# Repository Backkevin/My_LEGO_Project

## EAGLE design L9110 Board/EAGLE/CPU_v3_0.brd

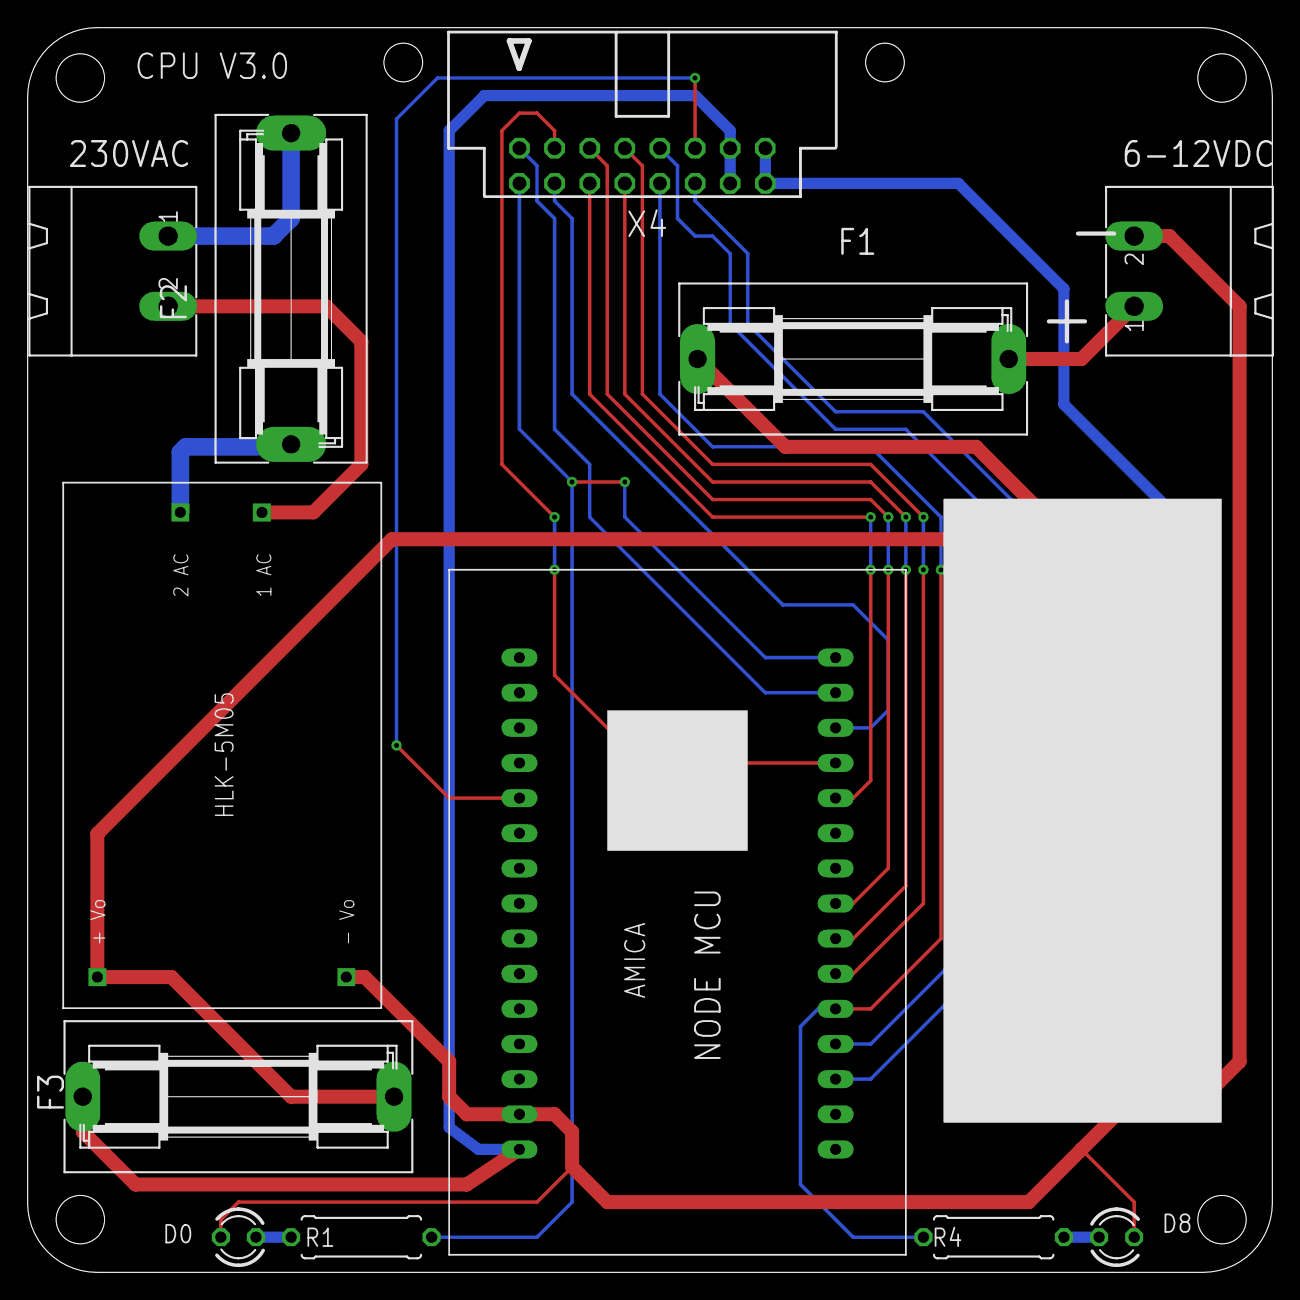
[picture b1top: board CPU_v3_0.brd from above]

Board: 2 copper layers, 90.0 x 90.0 mm, 13 parts (0 on the bottom side), 23 nets.

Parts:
6-12VDC, 230VAC: MSTBA2
D0, D8: LED3MM
F1, F2, F3: SH22,5A
R1, R4: 470R; 0309/10
U$1: NODEMCUESP8266
U$2: CP8-ADJ
U$3: 5VDC/5W; HLK-5M05
X4: 057-016-0

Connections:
+5VDC: F3.1, U$1.1, X4.13, X4.14
D0: R1.2, U$1.16, X4.1
D8: R4.2, U$1.26, X4.9
D9: U$1.11, X4.12
GND: D0.K, D8.K, U$1.2, U$2.OUT-, U$3.3, X4.15, X4.16
unnamed: D8.A, R4.1
unnamed: F3.2, U$2.OUT+, U$3.4
unnamed: U$1.19, X4.4
unnamed: D0.A, R1.1
unnamed: 230VAC.1, F2.2
unnamed: F2.1, U$3.1
unnamed: 230VAC.2, U$3.2
unnamed: 6-12VDC.1, F1.2
unnamed: F1.1, U$2.IN+
unnamed: 6-12VDC.2, U$2.IN-
unnamed: U$1.20, X4.5
unnamed: U$1.23, X4.6
unnamed: U$1.24, X4.7
unnamed: U$1.25, X4.8
RX: U$1.27, X4.10
SCL: U$1.17, X4.2
SDA: U$1.18, X4.3
TX: U$1.28, X4.11

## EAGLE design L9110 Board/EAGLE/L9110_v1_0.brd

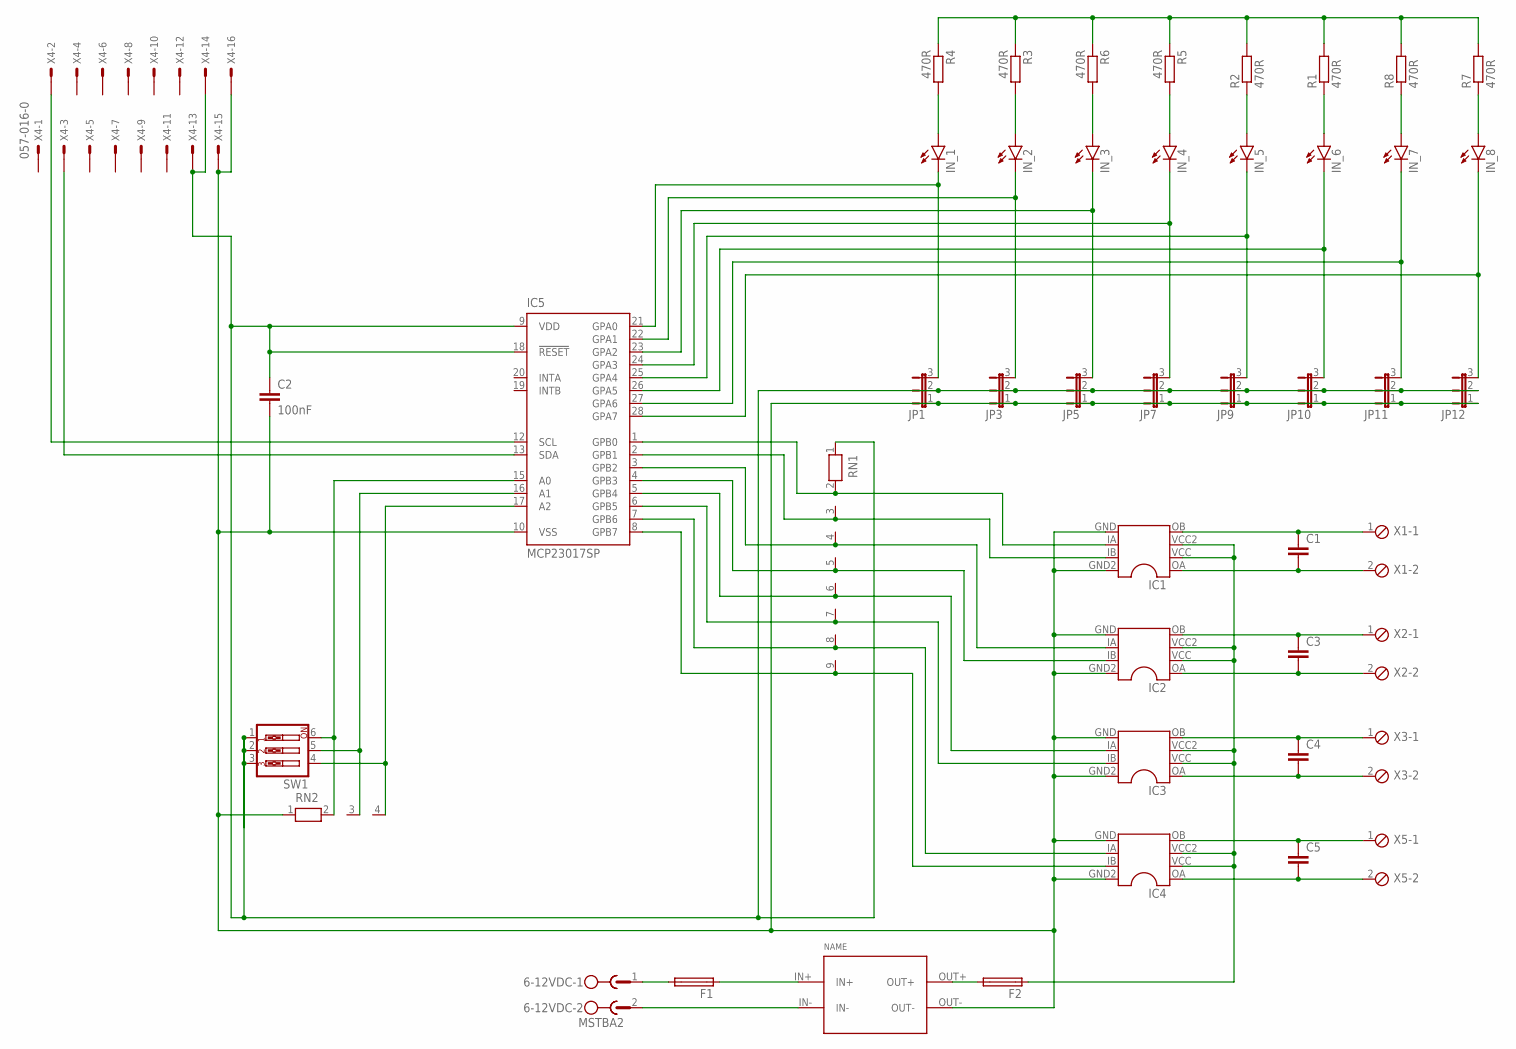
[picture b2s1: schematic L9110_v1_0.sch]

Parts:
6-12VDC: MSTBA2
C1, C3, C4, C5: C-EU025-024X044; C025-024X044
C2: 100nF; C025-024X044
F1, F2: SH22,5A
IC1, IC2, IC3, IC4: L9110
IC5: MCP23017SP; DIL28-3
IN_1, IN_2, IN_3, IN_4, IN_5, IN_6, IN_7, IN_8: LED3MM
JP1, JP3, JP5, JP7, JP9, JP10, JP11, JP12: JP2E; JP2
R1, R2, R3, R4, R5, R6, R7, R8: 470R; 0309/10
RN1: RN08; RN-9
RN2: RN03; RN-3
SW1: SW_DIP-3; EDG-03
U$2: CP8-ADJ
X1, X2, X3, X5: MPT2; 2POL254
X4: 057-016-0

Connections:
GND2: C2.2, IC1.GND (5), IC1.GND2 (8), IC2.GND (5), IC2.GND2 (8), IC3.GND (5), IC3.GND2 (8), IC4.GND (5), IC4.GND2 (8), IC5.10 (VSS), JP1.1, JP3.1, JP5.1, JP7.1, JP9.1, JP10.1, JP11.1, JP12.1, RN2.1, U$2.OUT-, X4.15, X4.16
unnamed: IC1.IA (6), IC5.1 (GPB0), RN1.2
unnamed: IC5.22 (GPA1), IN_2.K (C), JP3.3
unnamed: IC1.IB (7), IC5.2 (GPB1), RN1.3
unnamed: IC5.24 (GPA3), IN_4.K (C), JP7.3
unnamed: IC2.IA (6), IC5.3 (GPB2), RN1.4
unnamed: IC5.17 (A2), RN2.4, SW1.4
unnamed: IC5.26 (GPA5), IN_6.K (C), JP10.3
unnamed: IC2.IB (7), IC5.4 (GPB3), RN1.5
unnamed: IC5.28 (GPA7), IN_8.K (C), JP12.3
unnamed: IN_8.A, R7.1
unnamed: IN_7.A, R8.1
unnamed: IC3.IA (6), IC5.5 (GPB4), RN1.6
unnamed: IN_6.A, R1.1
unnamed: IC3.IB (7), IC5.6 (GPB5), RN1.7
unnamed: IC4.IA (6), IC5.7 (GPB6), RN1.8
unnamed: IC4.IB (7), IC5.8 (GPB7), RN1.9
unnamed: C1.1, IC1.OB (4), X1.1
unnamed: F2.1, IC1.VCC (2), IC1.VCC2 (3), IC2.VCC (2), IC2.VCC2 (3), IC3.VCC (2), IC3.VCC2 (3), IC4.VCC (2), IC4.VCC2 (3)
unnamed: C1.2, IC1.OA (1), X1.2
unnamed: C3.1, IC2.OB (4), X2.1
unnamed: IC5.21 (GPA0), IN_1.K (C), JP1.3
unnamed: C3.2, IC2.OA (1), X2.2
unnamed: IC5.23 (GPA2), IN_3.K (C), JP5.3
unnamed: C4.1, IC3.OB (4), X3.1
unnamed: IC5.25 (GPA4), IN_5.K (C), JP9.3
unnamed: C4.2, IC3.OA (1), X3.2
unnamed: IC5.27 (GPA6), IN_7.K (C), JP11.3
unnamed: C5.1, IC4.OB (4), X5.1
unnamed: IN_5.A, R2.1
unnamed: IN_4.A, R5.2
unnamed: IN_3.A, R6.2
unnamed: IN_2.A, R3.2
unnamed: IN_1.A, R4.2
unnamed: C5.2, IC4.OA (1), X5.2
unnamed: IC5.16 (A1), RN2.3, SW1.5
unnamed: 6-12VDC.1, F1.2
unnamed: F1.1, U$2.IN+
unnamed: 6-12VDC.2, U$2.IN-
unnamed: F2.2, U$2.OUT+
unnamed: IC5.12 (SCL), X4.2
unnamed: IC5.13 (SDA), X4.3
unnamed: IC5.15 (A0), RN2.2, SW1.6
VCC5.1: C2.1, IC5.9 (VDD), IC5.18 (!RESET), JP1.2, JP3.2, JP5.2, JP7.2, JP9.2, JP10.2, JP11.2, JP12.2, RN1.1, SW1.1, SW1.2, SW1.3, X4.13, X4.14
VCC5.2: R1.2, R2.2, R3.1, R4.1, R5.1, R6.1, R7.2, R8.2

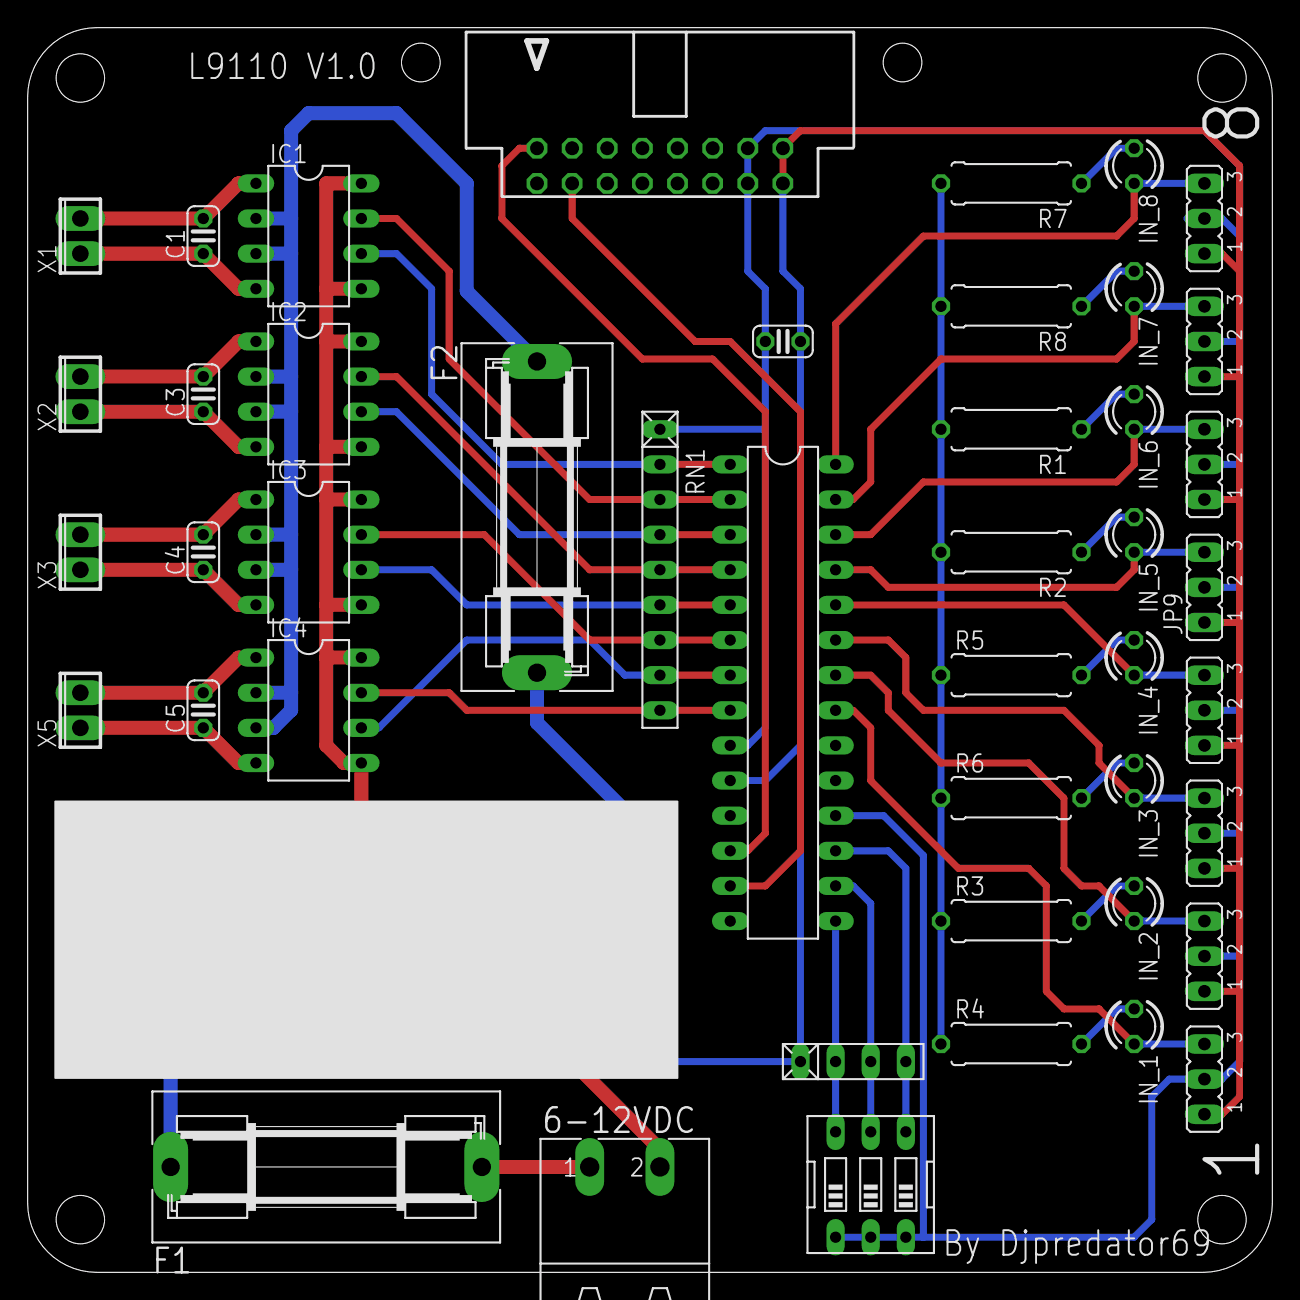
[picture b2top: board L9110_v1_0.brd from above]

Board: 2 copper layers, 90.0 x 90.0 mm, 46 parts (0 on the bottom side), 45 nets.

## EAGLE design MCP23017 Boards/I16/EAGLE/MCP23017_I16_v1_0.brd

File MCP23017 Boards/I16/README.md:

# MCP23017 Boards
+ I16
	+ V1.0
		* Work 50%
		* Partlist not OK
		* [GERBER FILES](https://github.com/Backkevin/My_LEGO_Project/tree/master/MCP23017%20Boards/I16/GERBER%20FILES)
		* [EAGLE FILES](https://github.com/Backkevin/My_LEGO_Project/tree/master/MCP23017%20Boards/I16/EAGLE)
		* [PDF FILES](https://github.com/Backkevin/My_LEGO_Project/tree/master/MCP23017%20Boards/I16/PDF)
	+ Work in progress !

### Partslist INPUT
                    
  Part Name   |      PIC      |   Part Info            | Part Quantity |   Part Link 
------------- | ------------- | ---------------------- | ------------- | -------------

### Partslist CPU
                    
  Part Name   |      PIC      |   Part Info            | Part Quantity |   Part Link 
------------- | ------------- | ---------------------- | ------------- | -------------

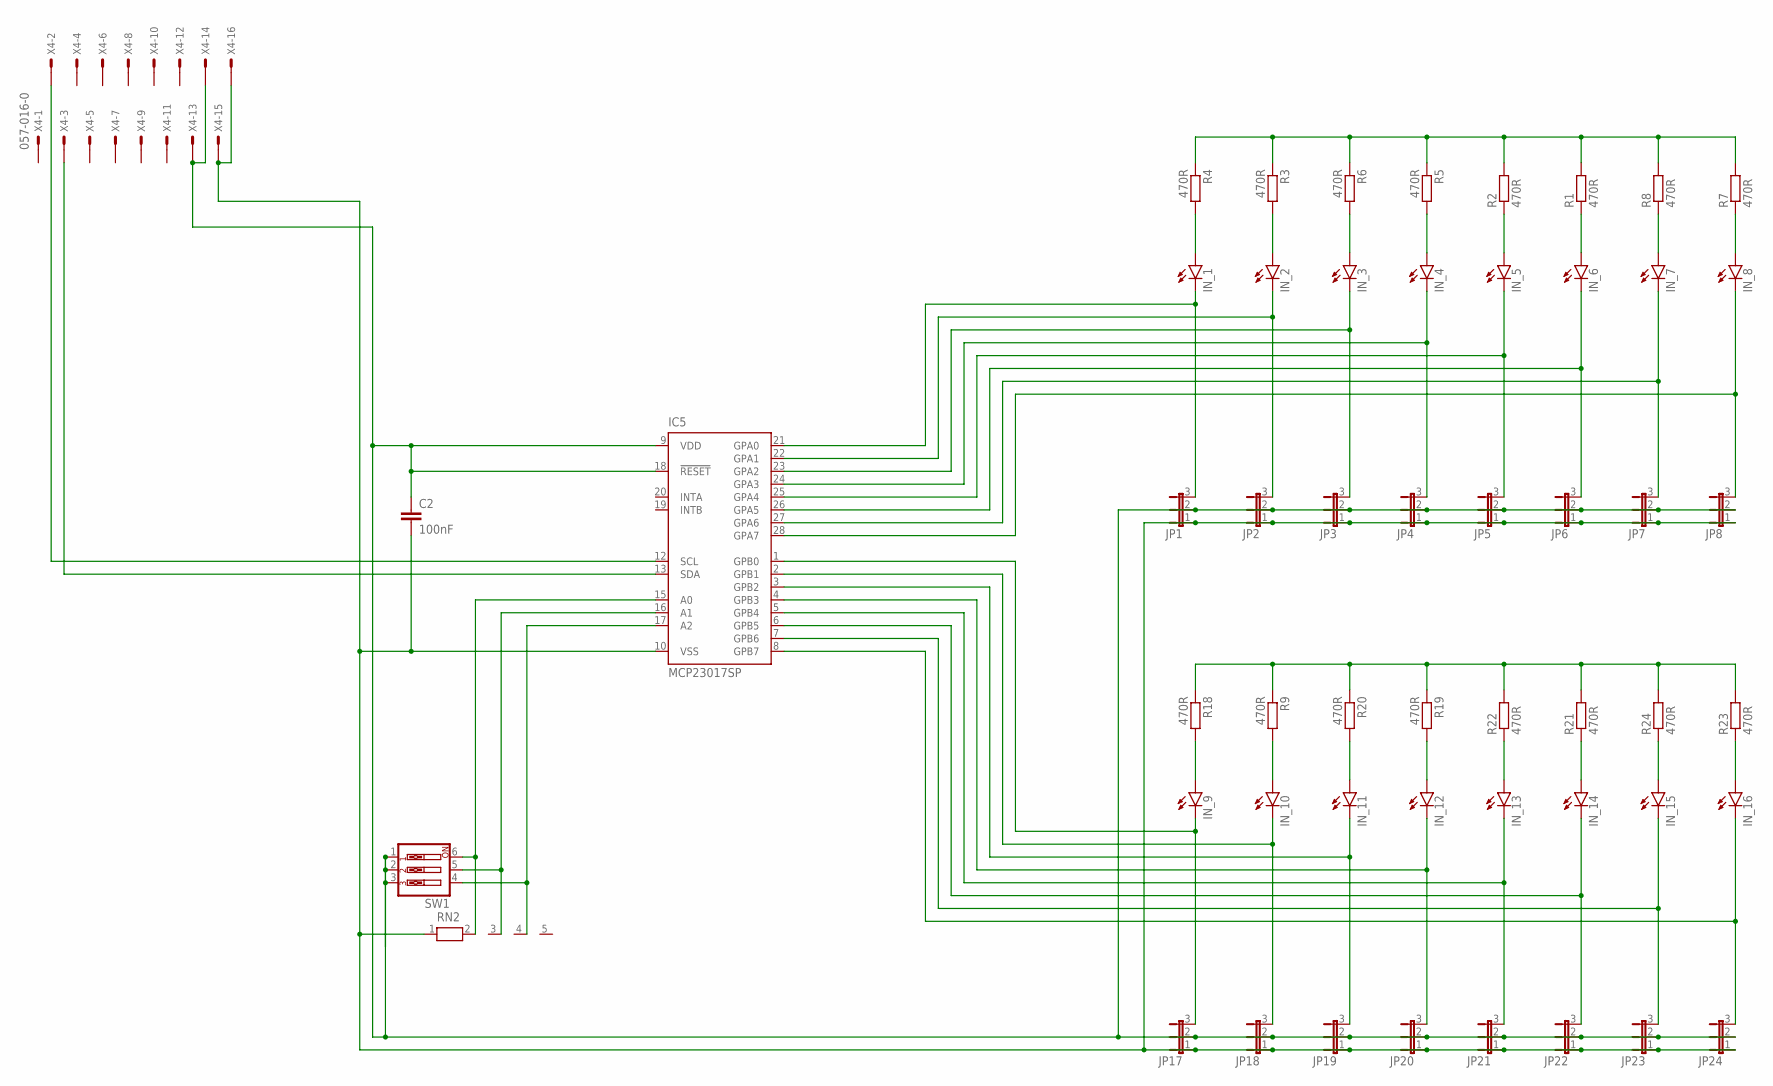
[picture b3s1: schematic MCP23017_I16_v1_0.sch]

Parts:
C2: 100nF; C025-024X044
IC5: MCP23017SP; DIL28-3
IN_1, IN_2, IN_3, IN_4, IN_5, IN_6, IN_7, IN_8, IN_9, IN_10, IN_11, IN_12, IN_13, IN_14, IN_15, IN_16: LED3MM
JP1, JP2, JP3, JP4, JP5, JP6, JP7, JP8, JP17, JP18, JP19, JP20, JP21, JP22, JP23, JP24: JP2E; JP2
R1, R2, R3, R4, R5, R6, R7, R8, R9, R18, R19, R20, R21, R22, R23, R24: 470R; 0309/10
RN2: RN04; RN-5
SW1: SW_DIP-3; EDG-03
X4: 057-016-0

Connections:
GND1: C2.2, IC5.10 (VSS), JP1.1, JP2.1, JP3.1, JP4.1, JP5.1, JP6.1, JP7.1, JP8.1, JP17.1, JP18.1, JP19.1, JP20.1, JP21.1, JP22.1, JP23.1, JP24.1, RN2.1, X4.15, X4.16
unnamed: IC5.21 (GPA0), IN_1.K (C), JP1.3
unnamed: IC5.15 (A0), RN2.2, SW1.6
unnamed: IC5.23 (GPA2), IN_3.K (C), JP3.3
unnamed: IC5.25 (GPA4), IN_5.K (C), JP5.3
unnamed: IC5.17 (A2), RN2.4, SW1.4
unnamed: IC5.27 (GPA6), IN_7.K (C), JP7.3
unnamed: IN_8.A, R7.1
unnamed: IN_7.A, R8.1
unnamed: IN_6.A, R1.1
unnamed: IC5.22 (GPA1), IN_2.K (C), JP2.3
unnamed: IC5.24 (GPA3), IN_4.K (C), JP4.3
unnamed: IC5.26 (GPA5), IN_6.K (C), JP6.3
unnamed: IC5.28 (GPA7), IN_8.K (C), JP8.3
unnamed: IN_5.A, R2.1
unnamed: IN_4.A, R5.2
unnamed: IN_3.A, R6.2
unnamed: IN_2.A, R3.2
unnamed: IN_1.A, R4.2
unnamed: IC5.16 (A1), RN2.3, SW1.5
unnamed: IC5.1 (GPB0), IN_9.K (C), JP17.3
unnamed: IC5.3 (GPB2), IN_11.K (C), JP19.3
unnamed: IC5.5 (GPB4), IN_13.K (C), JP21.3
unnamed: IC5.2 (GPB1), IN_10.K (C), JP18.3
unnamed: IC5.4 (GPB3), IN_12.K (C), JP20.3
unnamed: IC5.7 (GPB6), IN_15.K (C), JP23.3
unnamed: IC5.6 (GPB5), IN_14.K (C), JP22.3
unnamed: IC5.8 (GPB7), IN_16.K (C), JP24.3
unnamed: IN_16.A, R23.1
unnamed: IN_15.A, R24.1
unnamed: IN_14.A, R21.1
unnamed: IN_13.A, R22.1
unnamed: IN_12.A, R19.2
unnamed: IN_11.A, R20.2
unnamed: IN_10.A, R9.2
unnamed: IN_9.A, R18.2
unnamed: IC5.12 (SCL), X4.2
unnamed: IC5.13 (SDA), X4.3
VCC5.2: C2.1, IC5.9 (VDD), IC5.18 (!RESET), JP1.2, JP2.2, JP3.2, JP4.2, JP5.2, JP6.2, JP7.2, JP8.2, JP17.2, JP18.2, JP19.2, JP20.2, JP21.2, JP22.2, JP23.2, JP24.2, R1.2, R2.2, R3.1, R4.1, R5.1, R6.1, R7.2, R8.2, R9.1, R18.1, R19.1, R20.1, R21.2, R22.2, R23.2, R24.2, SW1.1, SW1.2, SW1.3, X4.13, X4.14

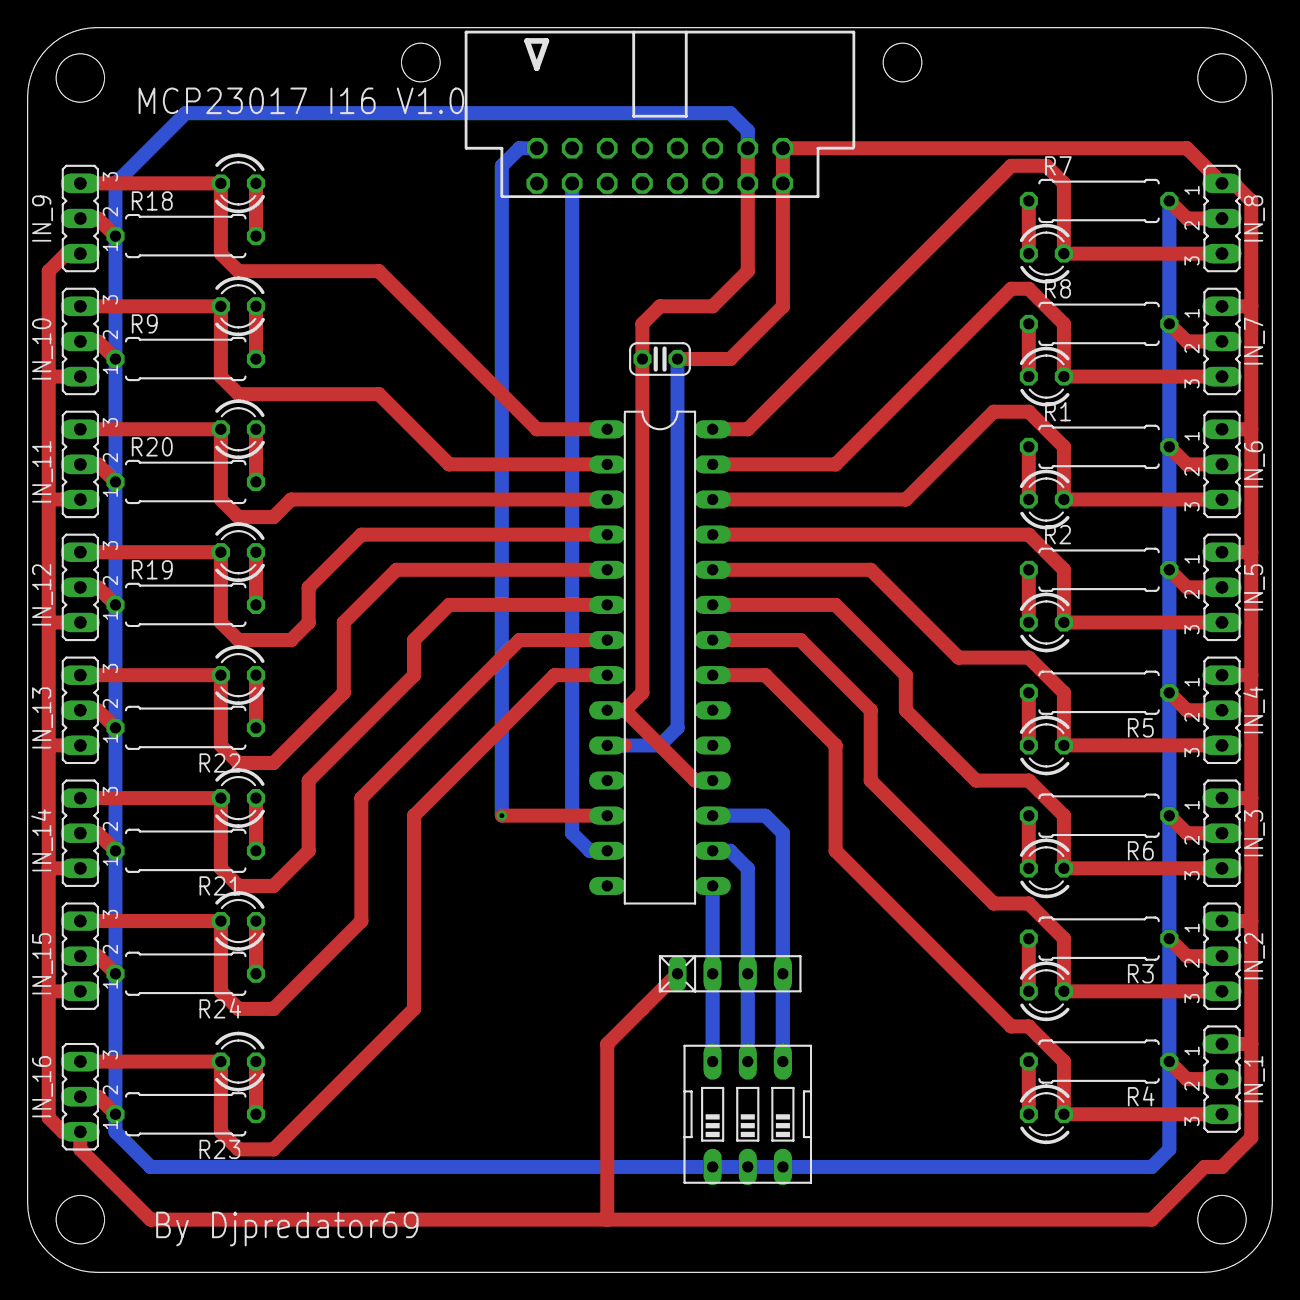
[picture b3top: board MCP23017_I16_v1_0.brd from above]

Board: 2 copper layers, 90.0 x 90.0 mm, 53 parts (0 on the bottom side), 39 nets.

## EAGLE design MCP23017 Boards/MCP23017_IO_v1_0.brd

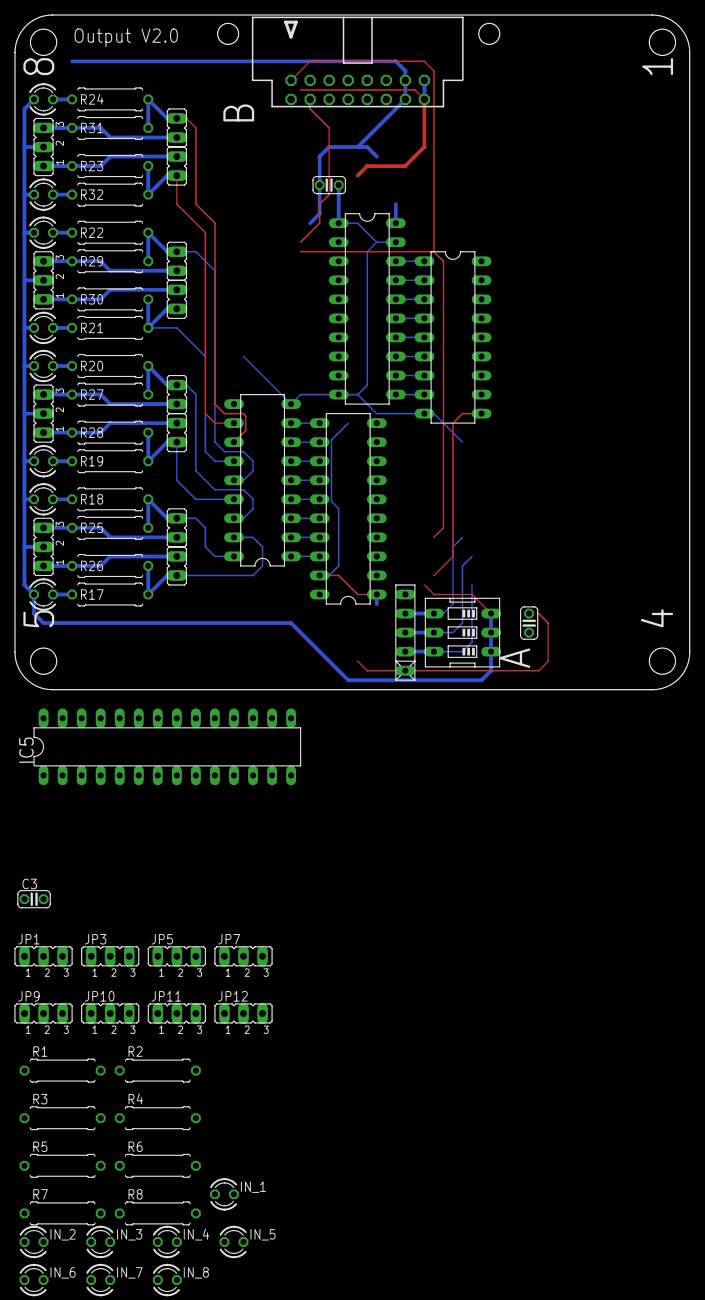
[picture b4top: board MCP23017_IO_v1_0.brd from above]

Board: 2 copper layers, 90.0 x 90.0 mm, 71 parts (0 on the bottom side), 80 nets.

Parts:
C2, C3, C6: 100nF; C025-024X044
IC1, IC2: DIL18
IC3, IC4: 74HC540N; DIL20
IC5: MCP23017SP; DIL28-3
IN_1, IN_2, IN_3, IN_4, IN_5, IN_6, IN_7, IN_8: LED3MM
JP1, JP2, JP3, JP4, JP5, JP6, JP7, JP8, JP9, JP10, JP11, JP12: JP2
JP17, JP18, JP19, JP20, JP21, JP22, JP23, JP24: JP1
R1, R2, R3, R4, R5, R6, R7, R8, R17, R18, R19, R20, R21, R22, R23, R24, R25, R26, R27, R28, R29, R30, R31, R32: 470R; 0309/10
RN2: RN-5
SIG_9, SIG_10, SIG_11, SIG_12, SIG_13, SIG_14, SIG_15, SIG_16: LED3MM
SW1: EDG-03
X4: 057-016-0

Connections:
GND2: C2.2, C3.1, C6.1, IC1.9, IC2.9, IC3.1, IC3.10, IC3.19, IC4.1, IC4.10, IC4.19, IC5.10, JP1.1, JP3.1, JP5.1, JP7.1, JP9.1, JP10.1, JP11.1, JP12.1, RN2.1, X4.15, X4.16
unnamed: IC2.18, IN_1.K, JP1.3
unnamed: IC2.17, IN_2.K, JP3.3
unnamed: IC2.16, IN_3.K, JP5.3
unnamed: IC2.15, IN_4.K, JP7.3
unnamed: IC2.14, IN_5.K, JP9.3
unnamed: IC5.17, RN2.4, SW1.4
unnamed: IC2.13, IN_6.K, JP10.3
unnamed: IC2.12, IN_7.K, JP11.3
unnamed: IC2.11, IN_8.K, JP12.3
unnamed: IN_8.A, R7.1
unnamed: IN_7.A, R8.1
unnamed: IC2.8, IC3.11
unnamed: IN_6.A, R1.1
unnamed: IC2.7, IC3.12
unnamed: IC2.6, IC3.13
unnamed: IC2.5, IC3.14
unnamed: IC2.4, IC3.15
unnamed: IC2.3, IC3.16
unnamed: IC2.2, IC3.17
unnamed: IC2.1, IC3.18
unnamed: IC3.2, IC5.21
unnamed: IC3.3, IC5.22
unnamed: IC3.4, IC5.23
unnamed: IC3.5, IC5.24
unnamed: IC3.6, IC5.25
unnamed: IC3.7, IC5.26
unnamed: IC3.8, IC5.27
unnamed: IC3.9, IC5.28
unnamed: IN_5.A, R2.1
unnamed: IN_4.A, R5.2
unnamed: IN_3.A, R6.2
unnamed: IN_2.A, R3.2
unnamed: IN_1.A, R4.2
unnamed: IC1.8, IC4.11
unnamed: IC5.16, RN2.3, SW1.5
unnamed: IC1.7, IC4.12
unnamed: IC1.6, IC4.13
unnamed: IC1.5, IC4.14
unnamed: IC1.4, IC4.15
unnamed: IC1.3, IC4.16
unnamed: IC1.2, IC4.17
unnamed: IC1.1, IC4.18
unnamed: IC4.2, IC5.1
unnamed: IC4.3, IC5.2
unnamed: IC4.4, IC5.3
unnamed: IC4.5, IC5.4
unnamed: IC4.6, IC5.5
unnamed: IC4.7, IC5.6
unnamed: IC4.8, IC5.7
unnamed: IC4.9, IC5.8
unnamed: IC1.18, JP17.2, R18.2, R25.1
unnamed: IC1.17, JP24.2, R17.2, R26.1
unnamed: R18.1, SIG_10.K
unnamed: R17.1, SIG_9.K
unnamed: IC1.16, JP18.2, R20.2, R27.1
unnamed: IC1.15, JP19.2, R19.2, R28.1
unnamed: IC1.14, JP20.2, R22.2, R29.1
unnamed: R20.1, SIG_12.K
unnamed: R19.1, SIG_11.K
unnamed: IC1.13, JP21.2, R21.2, R30.1
unnamed: R22.1, SIG_14.K
unnamed: R21.1, SIG_13.K
unnamed: IC1.12, JP22.2, R24.2, R31.1
unnamed: R24.1, SIG_16.K
unnamed: R23.1, SIG_15.K
unnamed: JP2.3, JP17.1, R25.2
unnamed: JP2.1, JP24.1, R26.2
unnamed: JP4.3, JP18.1, R27.2
unnamed: JP4.1, JP19.1, R28.2
unnamed: JP6.3, JP20.1, R29.2
unnamed: JP6.1, JP21.1, R30.2
unnamed: JP8.3, JP22.1, R31.2
unnamed: JP8.1, JP23.1, R32.2
unnamed: IC5.12, X4.2
unnamed: IC1.11, JP23.2, R23.2, R32.1
unnamed: IC5.13, X4.3
unnamed: IC5.15, RN2.2, SW1.6
VCC5.1: C2.1, C3.2, C6.2, IC1.10, IC2.10, IC3.20, IC4.20, IC5.9, IC5.18, JP1.2, JP2.2, JP3.2, JP4.2, JP5.2, JP6.2, JP7.2, JP8.2, JP9.2, JP10.2, JP11.2, JP12.2, SIG_9.A, SIG_10.A, SIG_11.A, SIG_12.A, SIG_13.A, SIG_14.A, SIG_15.A, SIG_16.A, SW1.1, SW1.2, SW1.3, X4.13, X4.14
VCC5.2: R1.2, R2.2, R3.1, R4.1, R5.1, R6.1, R7.2, R8.2
